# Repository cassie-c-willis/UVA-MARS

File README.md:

# MARS-17-18
2017-2018 MARS Electrical and Software Repository

This was a joint collaboration effort project on which I worked on the electrical design and embedded code using the SPIN language.

See portfolio pages for a visual summary of completed work.

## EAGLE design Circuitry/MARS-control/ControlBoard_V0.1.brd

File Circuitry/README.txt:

UVA MARS Control Board Specifications
Updated: 12-3-2016

Overall:
* The overall purpose of the control board is to connect the wireless communications between the software on a computer and the motors on the robot. 

XBEE:
* The XBEE chip is a wireless communication chip that connects to the software. 
* The XBEE receives up to 8 bytes of information from the computer and communicates those bytes to Propeller 1. 

Joystick Control Mapping:
* Each byte or bit of information corresponds to a function on the joystick. The propeller chips have software loaded onto them to respond to given inputs from the joystick. 
In total there are 14 bytes. Byte 1 is the start byte, bytes 2 - 7 represent the state of the right joystick, bytes 8-13 represent the state of the left joystick, byte 14 is the end byte. 
START BYTE
* First byte: all 1's, (255 in decimal, 11111111 in binary) showing the joystick is connected 
RIGHT JOYSTICK
* Second byte: 
  o Bit 1: Button 1
  o Bit 2: Button 2
  o Bit 3: Button 3
  o Bit 4: Button 4
  o Bit 5: Button 5
  o Bit 6: Button 6
  o Bit 7: Button 7
  o Bit 8: Button 8
* Third Byte:
  o Bit 1: Button 9
  o Bit 2: Button 10
  o Bit 3: Button 11
  o Bit 4: Button 12
  o Bit 5: Pad up
  o Bit 6: Pad down
  o Bit 7: Pad right
  o Bit 8: Pad left
* Fourth Byte: Y-axis of main stick, 11111101 (253 in decimal) is all the way forward, 00000000 (0 in decimal) is the way backward, 01111111 is centered (127 in decimal). 
* Fifth Byte: X-axis of main stick, 11111101 (253 in decimal) is all the way right, 00000000 (0 in decimal) is the way left, 01111111 is centered (127 in decimal). 
* Sixth Byte: Rotation of main stick, 11111101 (253 in decimal) is rotated all the way to the right, 00000000 (0 in decimal) is rotated all the way to the left, 01111111 (127 in decimal) is no rotation
* Seventh Byte: Slider, 11111101 (253 in decimal) is all the way up, 00000000 (0 in decimal) is all the way down
LEFT JOYSTICK
* Eighth byte: 
  o Bit 1: Button 1
  o Bit 2: Button 2
  o Bit 3: Button 3
  o Bit 4: Button 4
  o Bit 5: Button 5
  o Bit 6: Button 6
  o Bit 7: Button 7
  o Bit 8: Button 8
* Ninth Byte:
  o Bit 1: Button 9
  o Bit 2: Button 10
  o Bit 3: Button 11
  o Bit 4: Button 12
  o Bit 5: Pad up
  o Bit 6: Pad down
  o Bit 7: Pad right
  o Bit 8: Pad left
* Tenth Byte: Y-axis of main stick, 11111101 (253 in decimal) is all the way forward, 00000000 (0 in decimal) is the way backward, 01111111 is centered (127 in decimal). 
* Eleventh Byte: X-axis of main stick, 11111101 (253 in decimal) is all the way right, 00000000 (0 in decimal) is the way left, 01111111 is centered (127 in decimal). 
* Twelfth Byte: Rotation of main stick, 11111101 (253 in decimal) is rotated all the way to the right, 00000000 (0 in decimal) is rotated all the way to the left, 01111111 (127 in decimal) is no rotation
* Thirteenth Byte: Slider, 11111101 (253 in decimal) is all the way up, 00000000 (0 in decimal) is all the way down
END BYTE
* Fourteenth Byte: 11111110 (254 in decimal) verifying that the signal is correct

Propeller 1:
* Receives motor communication bytes from the XBEE
* Sends that information to Propeller 2
* Mainly present so a byway between the XBEE and Propeller 2 
* Can be used to run sensors if the decision is made to add sensors to the robot later on

Propeller 2:
* Receives motor communication bytes from the XBEE
* Includes software that understands what to do with the information from the byte string
* Controls each of the motors through a signal wire to make the motors operate in a certain way such that the robot performs certain actions

Optoisolator:
* Creates optical instead of electrical communication 
* Primarily used to prevent brownouts on the board – also done through motors but this is an added measure of safety
* Connected between Propeller 2 and the H-Bridge supply wire

3.3V Voltage Regulator:
* Regulates the voltage from a 5-volt input signal to a 3.3-volt output signal
* Sends the 3.3v signal to the XBEE and the ADC chip

H-Bridge Signal Wire:
* Sends the signals to perform certain commands from Propeller 2 to the motors

Motor Power Connector:
* Provides 5 volts of power to the board
* These 5 volts are sent to the 3.3v voltage regulator to power the XBEE and ADC

Control Power Connector:
* Provides 12 volts of power to the board
* These 12 volts are used to power both of the propeller chips
* Also currently connected to a 5-volt regulator which is no longer in use in the board but is still present in the schematic

XBEE Reset Button:
* Resets the XBEE chip

Propeller Reset Button:
* Resets both of the Propeller chips

ADC:
* Analog-to-Digital Converter
* Used to hook up sensors and communicate to the sensors from Propeller 2
* Not currently in use because sensors not currently present on the robot

Other Components:
* Various resistors and capacitors are also included in the control board to help regulate the overall power flow
* Various LED’s are used on the board for testing purposes and to ensure that each element in the control board is operating properly

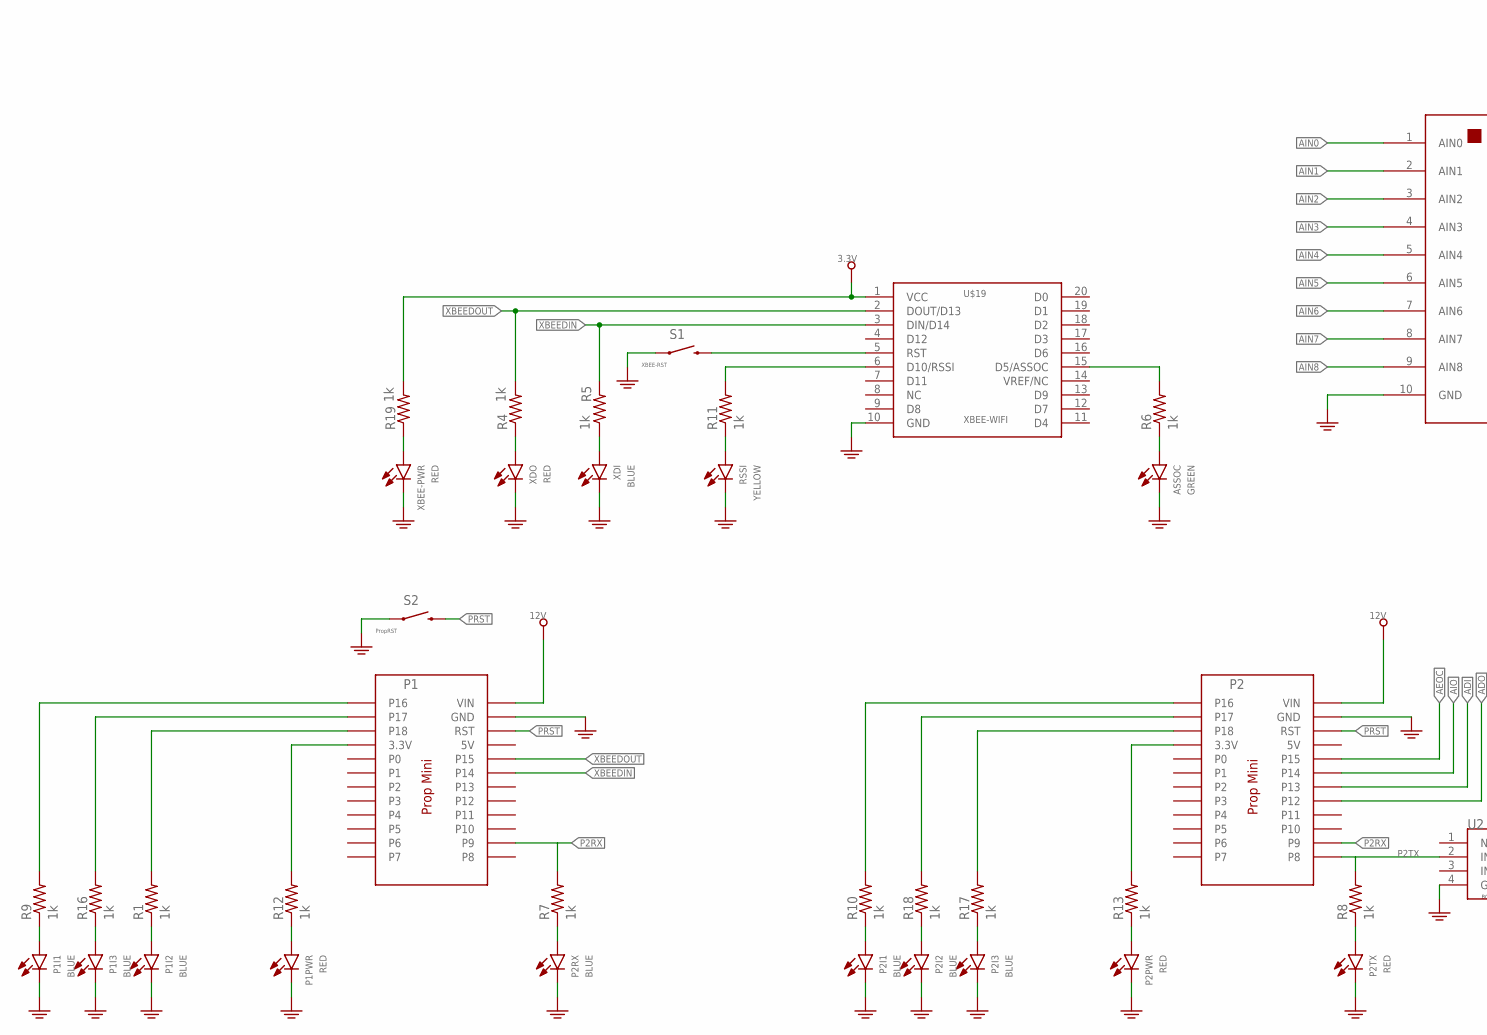
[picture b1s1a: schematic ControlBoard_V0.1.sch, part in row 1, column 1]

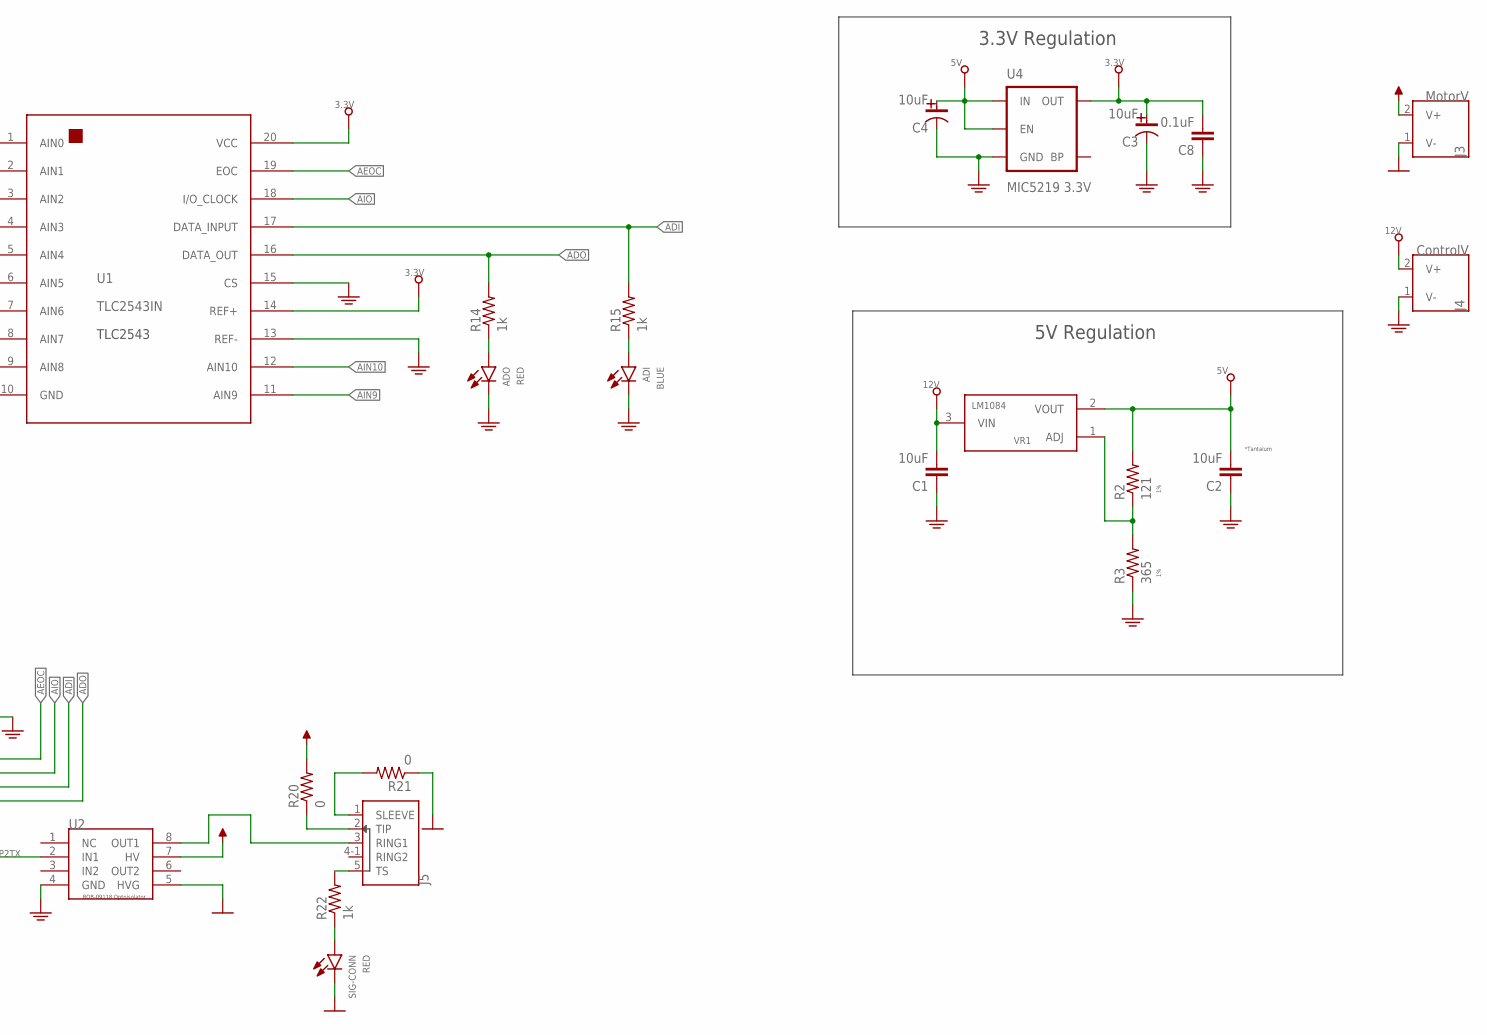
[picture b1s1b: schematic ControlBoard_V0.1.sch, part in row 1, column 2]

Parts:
ADI: BLUE; 0603
ADO: RED; 0603
ASSOC: GREEN; 0603
C1, C2: 10uF; 0603
C3, C4: 10uF; 0603-POL
C8: 0.1uF; 0603
J3: MotorV; PJ-002BH-SMT
J4: ControlV; PJ-037A
J5: SJ1-42535TS; SJ1-42534-SMT
P1, P2: PROP-MINI
P1I1, P1I2, P1I3, P2I1, P2I2, P2I3, P2RX: BLUE; 0603
P1PWR, P2PWR, P2TX: RED; 0603
R1, R4, R5, R6, R7, R8, R9, R10, R11, R12, R13, R14, R15, R16, R17, R18, R19, R22: 1k; 0603
R2: 121; 0603
R3: 365; 0603
R20, R21: 0; 0603
RSSI: YELLOW; 0603
S1: XBEE-RST; TACTILE_SWITCH_SMD-2
S2: PropRST; TACTILE_SWITCH_SMD-2
SIG-CONN: RED; 0603
U1: TLC2543IN; DIL-20
U2: BOB-09118; DIL08-0.1P-6W
U4: MIC5219 3.3V; SOT23-5
U$19: XBEE-WIFI; XBEE-STD
VR1: LM1084; TO-220
XBEE-PWR: RED; 0603
XDI: BLUE; 0603
XDO: RED; 0603

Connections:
3.3V: C3.2, C8.2, R19.2, U1.14 (REF+), U1.20 (VCC), U4.5 (OUT), U$19.1 (VCC)
5V: C2.2, C4.2, R2.2, U4.1 (IN), U4.3 (EN), VR1.2 (VOUT)
12V: C1.2, J4.2 (V+), P1.VIN, P2.VIN, VR1.3 (VIN)
ADI: P2.P13, R15.2, U1.17 (DATA_INPUT)
ADO: P2.P12, R14.2, U1.16 (DATA_OUT)
AEOC: P2.P15, U1.19 (EOC)
AIN0: U1.1 (AIN0)
AIN1: U1.2 (AIN1)
AIN2: U1.3 (AIN2)
AIN3: U1.4 (AIN3)
AIN4: U1.5 (AIN4)
AIN5: U1.6 (AIN5)
AIN6: U1.7 (AIN6)
AIN7: U1.8 (AIN7)
AIN8: U1.9 (AIN8)
AIN9: U1.11 (AIN9)
AIN10: U1.12 (AIN10)
AIO: P2.P14, U1.18 (I/O_CLOCK)
GND: ADI.OUT, ADO.OUT, ASSOC.OUT, C1.1, C2.1, C3.1, C4.1, C8.1, J4.1 (V-), P1.GND, P1I1.OUT, P1I2.OUT, P1I3.OUT, P1PWR.OUT, P2.GND, P2I1.OUT, P2I2.OUT, P2I3.OUT, P2PWR.OUT, P2RX.OUT, P2TX.OUT, R3.1, RSSI.OUT, S1.2 (1), S2.2 (1), U1.10 (GND), U1.13 (REF-), U1.15 (CS), U2.4 (GND), U4.2 (GND), U$19.10 (GND), XBEE-PWR.OUT, XDI.OUT, XDO.OUT
GND2: J3.1 (V-), R21.1, SIG-CONN.OUT, U2.5 (HVG)
unnamed: R4.1, XDO.IN
unnamed: P1I1.IN, R9.1
unnamed: P1.P18, R1.2
unnamed: ADO.IN, R14.1
unnamed: R11.1, RSSI.IN
unnamed: ADI.IN, R15.1
unnamed: R5.1, XDI.IN
unnamed: J5.3 (RING1), U2.8 (OUT1)
unnamed: R6.2, U$19.15 (D5/ASSOC)
unnamed: ASSOC.IN, R6.1
unnamed: P1.3.3V, R12.2
unnamed: P1I3.IN, R16.1
unnamed: P2.3.3V, R13.2
unnamed: P1I2.IN, R1.1
unnamed: P1PWR.IN, R12.1
unnamed: R19.1, XBEE-PWR.IN
unnamed: J5.1 (SLEEVE), R21.2
unnamed: P2RX.IN, R7.1
unnamed: P2I1.IN, R10.1
unnamed: S1.1 (2), U$19.5 (RST)
unnamed: R2.1, R3.2, VR1.1 (ADJ)
unnamed: R11.2, U$19.6 (D10/RSSI)
unnamed: P1.P16, R9.2
unnamed: P2I2.IN, R18.1
unnamed: P2I3.IN, R17.1
unnamed: P1.P17, R16.2
unnamed: P2PWR.IN, R13.1
unnamed: P2TX.IN, R8.1
unnamed: J5.2 (TIP), R20.1
unnamed: R22.1, SIG-CONN.IN
unnamed: J5.5 (TS), R22.2
P2RX: P1.P9, P2.P9, R7.2
P2TX: P2.P8, R8.2, U2.2 (IN1)
PRST: P1.RST, P2.RST, S2.1 (2)
VCC2: J3.2 (V+), R20.2, U2.7 (HV)
XBEEDIN: P1.P14, R5.2, U$19.3 (DIN/D14)
XBEEDOUT: P1.P15, R4.2, U$19.2 (DOUT/D13)

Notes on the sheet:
*Tantalum
5V Regulation
3.3V Regulation

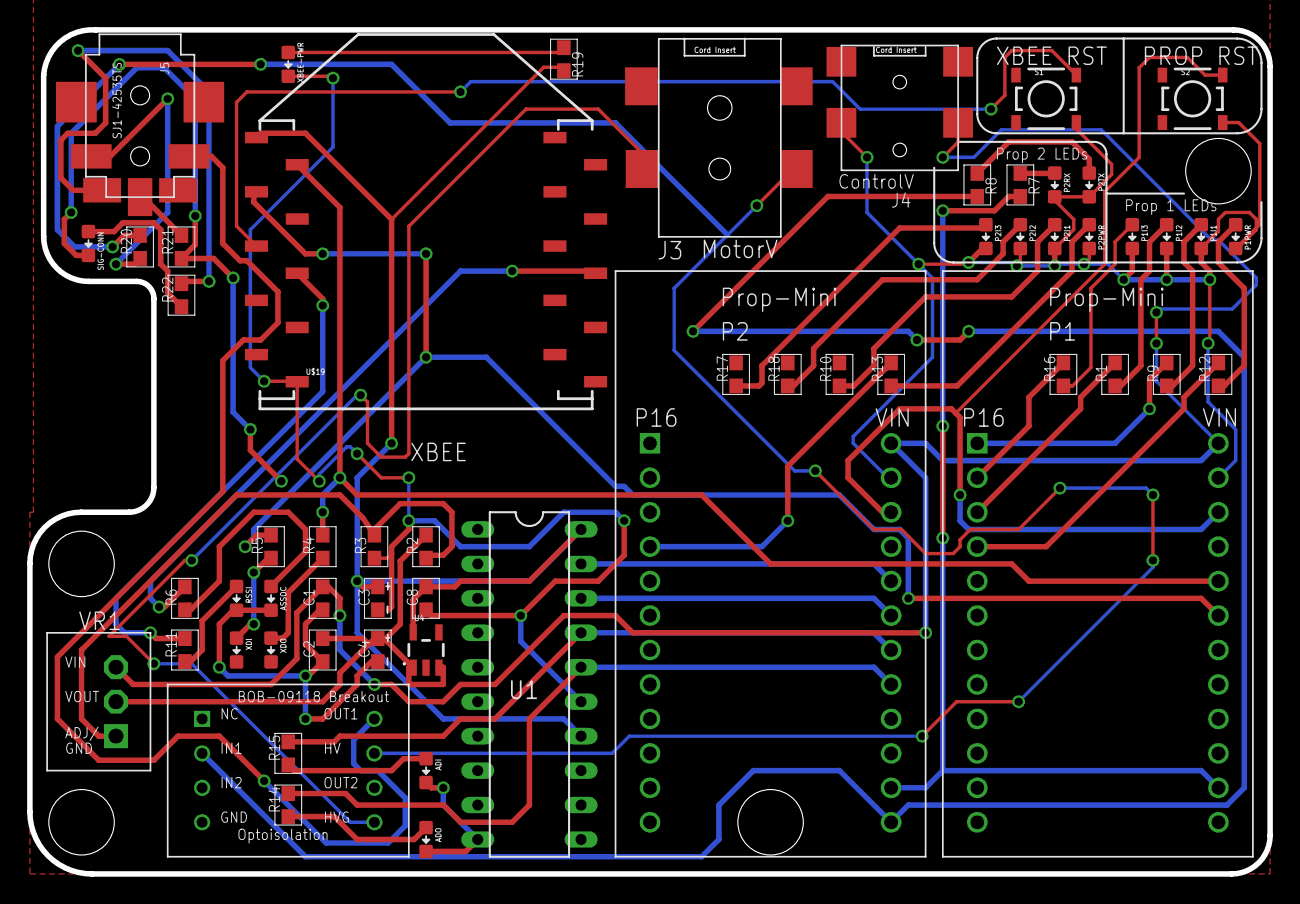
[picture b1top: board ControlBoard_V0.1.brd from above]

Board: 2 copper layers, 91.4 x 62.2 mm, 57 parts (0 on the bottom side), 46 nets.

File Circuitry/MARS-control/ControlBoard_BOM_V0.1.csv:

"Qty";"Value";"Device";"Package";"Parts";"Description";"CAP-TYPE";"MNT";"PROD_ID";"VALUE";
"2";"0";"R0603";"0603";"R20, R21";"";"";"";"";"";
"1";"0.1uF";"C0603";"0603";"C8";"";"";"";"";"";
"2";"10uF";"C-POL-T";"0603-POL";"C3, C4";"";"TANTALUM";"";"";"";
"2";"10uF";"C0603";"0603";"C1, C2";"";"";"";"";"";
"1";"121";"R0603";"0603";"R2";"";"";"";"";"";
"18";"1k";"R0603";"0603";"R1, R4, R5, R6, R7, R8, R9, R10, R11, R12, R13, R14, R15, R16, R17, R18, R19, R22";"";"";"";"";"";
"1";"365";"R0603";"0603";"R3";"";"";"";"";"";
"9";"BLUE";"LED-STD";"0603";"ADI, P1I1, P1I2, P1I3, P2I1, P2I2, P2I3, P2RX, XDI";"";"";"";"";"";
"1";"BOB-09118";"BOB-09118";"DIL08-0.1P-6W";"U2";"";"";"";"";"";
"1";"ControlV";"SINGLE-LINEA";"PJ-037A";"J4";"4UCON Part Num: 18742";"";"";"";"";
"1";"GREEN";"LED-STD";"0603";"ASSOC";"";"";"";"";"";
"1";"LM1084";"LM1084";"TO-220";"VR1";"";"";"";"";"";
"1";"MIC5219 3.3V";"V_REG_MIC52193.3V";"SOT23-5";"U4";"V_REG MIC5219";"";"";"VREG-09872";"MIC5219 3.3V";
"1";"MotorV";"SINGLE-LINE-TR";"PJ-002BH-SMT";"J3";"4UCON Part Num: 18742";"";"";"";"";
"2";"PROP-MINI";"PROP-MINI";"PROP-MINI";"P1, P2";"";"";"";"";"";
"1";"PropRST";"SWITCH-MOMENTARY-2SMD-2";"TACTILE_SWITCH_SMD-2";"S2";"Various NO switches- pushbuttons, reed, etc";"";"";"SWCH-09213";"";
"7";"RED";"LED-STD";"0603";"ADO, P1PWR, P2PWR, P2TX, SIG-CONN, XBEE-PWR, XDO";"";"";"";"";"";
"1";"SJ1-42535TS";"SJ1-42535TS";"SJ1-42534-SMT";"J5";"";"";"SMT";"";"";
"1";"TLC2543IN";"TLC2543IN";"DIL-20";"U1";"";"";"";"";"";
"1";"XBEE-RST";"SWITCH-MOMENTARY-2SMD-2";"TACTILE_SWITCH_SMD-2";"S1";"Various NO switches- pushbuttons, reed, etc";"";"";"SWCH-09213";"";
"1";"XBEE-WIFI";"XBEE-WIFI";"XBEE-STD";"U$19";"";"";"";"";"";
"1";"YELLOW";"LED-STD";"0603";"RSSI";"";"";"";"";"";

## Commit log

2017-09-10 adding all files from last year
2017-09-10 added name text
2017-09-10 Added Dennis
    I added Dennis
2017-09-10 added text file
2017-09-10 Added name(Hua)
2017-09-10 My info
2017-09-10 NickC
    Name
2017-09-10 Added name text file
2017-09-10 name
2017-09-10 addedName
2017-09-10 Name and Major (Hua)
2017-09-10 Added second name file
2017-09-10 added more information
2017-09-10 added Major_Vance
2017-09-10 added new text file
2017-09-10 added more info
2017-09-12 added member info
2017-09-12 reorganization of files
2017-09-15 added changes
2017-09-15 added info
2017-09-15 added eagle library files
2017-09-15 sam files
2017-10-20 added name file
2018-02-09 main propeller code on motorTesting.spin
2018-02-18 most recent code uploaded
2018-03-08 Alright, I've converted the Spin files in C++ files. They aren't as readable as they could be, but they compile just fine using Propellor-GCC (I built the .side project file with SimpleIDE, which is 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
2018-04-13 added next-gen files
2018-04-13 Added basic motor functions, untested
2018-04-15 Robot moves now, added right screw and bucket
2018-04-19 finished getting the robot moving
2018-04-20 The LIDAR code works pretty well, although it'll need filtering to be less erratic.
2018-05-08 Most of progress for potentiometers is done.
2018-05-09 finished bucket active control
2018-09-05 Create motorTestC
2020-07-17 Visual Summary of work done on NASA MARS team

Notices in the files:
parts and their libraries:
SparkFun-Electromechanical: Licensing: Creative Commons ShareAlike 4.0 International - https://creativecommons.org/licenses/by-sa/4.0
